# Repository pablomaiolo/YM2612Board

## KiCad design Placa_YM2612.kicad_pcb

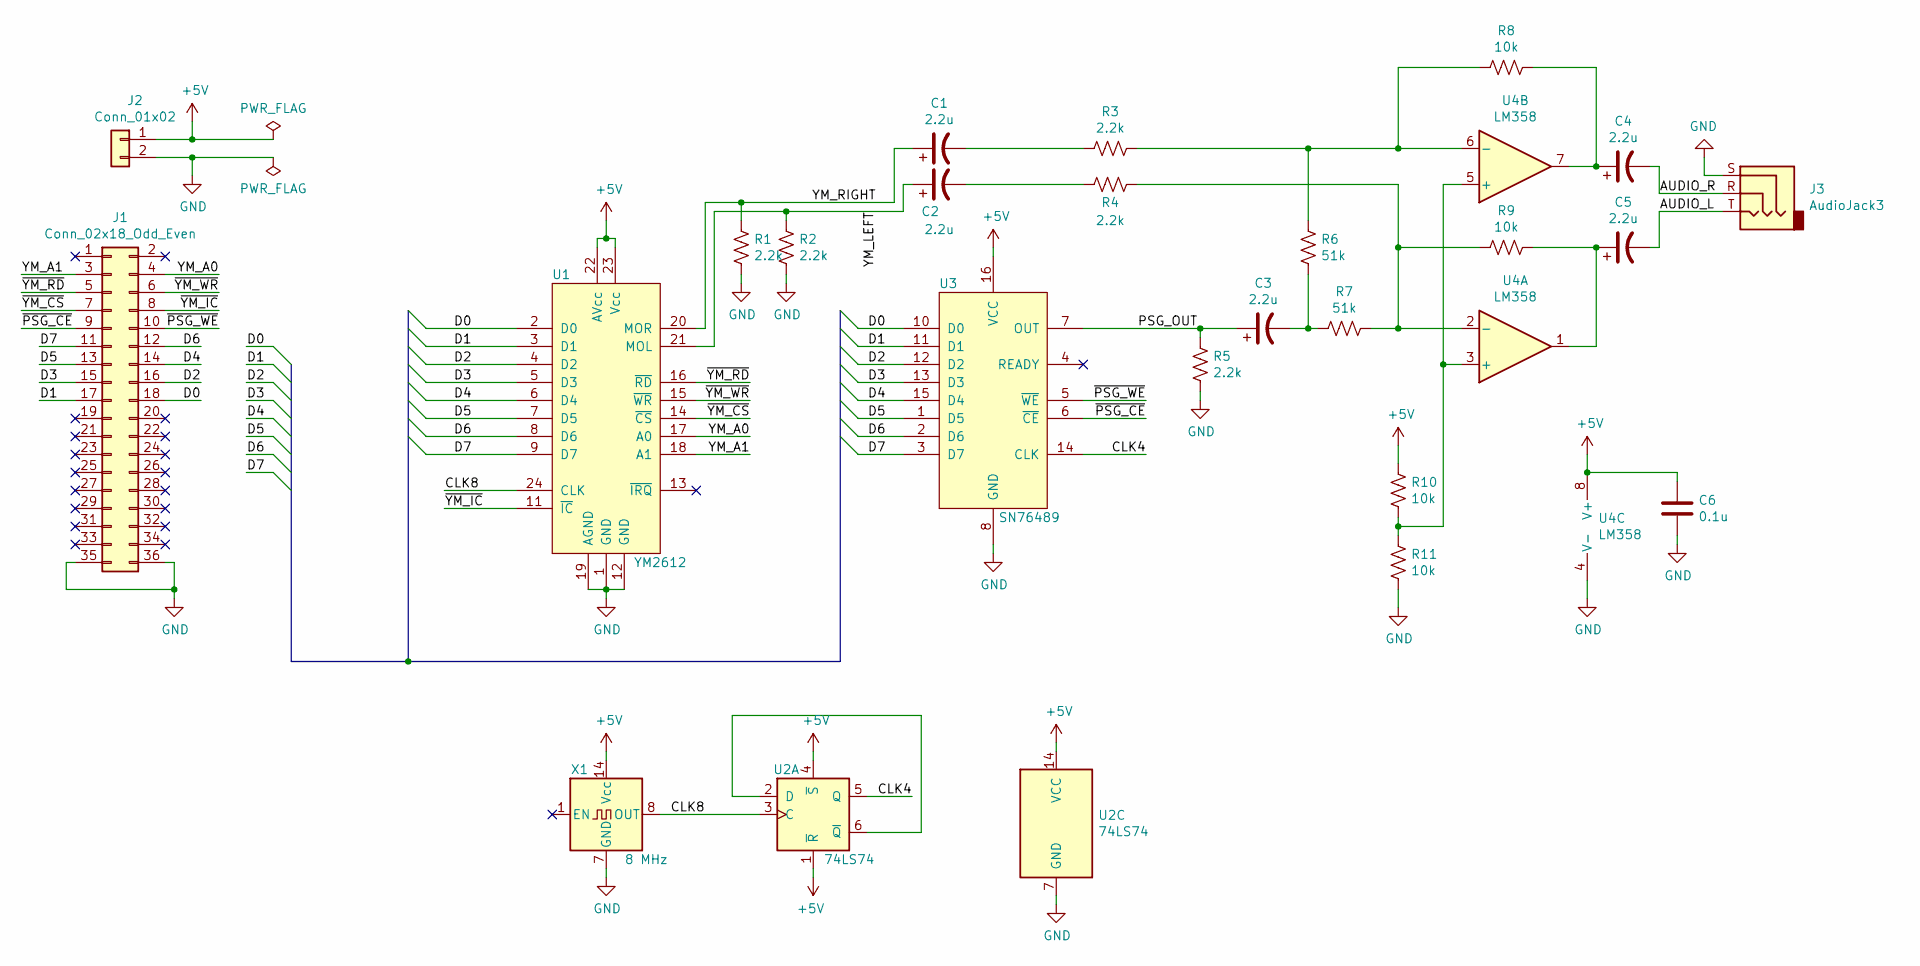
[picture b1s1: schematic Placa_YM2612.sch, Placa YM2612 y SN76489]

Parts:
C1, C2, C3, C4, C5: 2.2u; CP_Radial_D5.0mm_P2.50mm
C6: 0.1u; C_Disc_D5.0mm_W2.5mm_P2.50mm
J1: Conn_02x18_Odd_Even; PinHeader_2x18_P2.54mm_Vertical
J2: Conn_01x02; PinHeader_1x02_P2.54mm_Vertical
J3: AudioJack3; Placa_YM2612
R1, R2, R3, R4, R5: 2.2k; R_Axial_DIN0207_L6.3mm_D2.5mm_P10.16mm_Horizontal
R6, R7: 51k; R_Axial_DIN0207_L6.3mm_D2.5mm_P10.16mm_Horizontal
R8, R9, R10, R11: 10k; R_Axial_DIN0207_L6.3mm_D2.5mm_P10.16mm_Horizontal
U1: YM2612; DIP-24_W15.24mm_Socket_LongPads
U2: 74LS74; DIP-14_W7.62mm_LongPads
U3: SN76489; DIP-16_W7.62mm_Socket_LongPads
U4: LM358; DIP-8_W7.62mm_LongPads
X1: 8 MHz; Oscillator_DIP-14

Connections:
+5V: C6.1, J2.1, R10.1, U1.22 (AVcc), U1.23 (Vcc), U2.1 (~R), U2.4 (~S), U2.14 (VCC), U3.16 (VCC), U4.8 (V+), X1.14 (Vcc)
/AUDIO_L: C5.2, J3.T
/AUDIO_R: C4.2, J3.R
/CLK4: U2.5 (Q), U3.14 (CLK)
/CLK8: U1.24 (CLK), U2.3 (C), X1.8 (OUT)
/D0: J1.18, U1.2 (D0), U3.10 (D0)
/D1: J1.17, U1.3 (D1), U3.11 (D1)
/D2: J1.16, U1.4 (D2), U3.12 (D2)
/D3: J1.15, U1.5 (D3), U3.13 (D3)
/D4: J1.14, U1.6 (D4), U3.15 (D4)
/D5: J1.13, U1.7 (D5), U3.1 (D5)
/D6: J1.12, U1.8 (D6), U3.2 (D6)
/D7: J1.11, U1.9 (D7), U3.3 (D7)
/PSG_OUT: C3.1, R5.1, U3.7 (OUT)
/YM_A0: J1.4, U1.17 (A0)
/YM_A1: J1.3, U1.18 (A1)
/YM_LEFT: C2.1, R2.1, U1.21 (MOL)
/YM_RIGHT: C1.1, R1.1, U1.20 (MOR)
/~PSG_CE: J1.9, U3.6 (~CE)
/~PSG_WE: J1.10, U3.5 (~WE)
/~YM_CS: J1.7, U1.14 (~CS)
/~YM_IC: J1.8, U1.11 (~IC)
/~YM_RD: J1.5, U1.16 (~RD)
/~YM_WR: J1.6, U1.15 (~WR)
GND: C6.2, J1.35, J1.36, J2.2, J3.S, R1.2, R2.2, R5.2, R11.2, U1.1 (GND), U1.12 (GND), U1.19 (AGND), U2.7 (GND), U3.8 (GND), U4.4 (V-), X1.7 (GND)
unnamed: C1.2, R3.2
unnamed: C2.2, R4.2
unnamed: C3.2, R6.2, R7.2
unnamed: C4.1, R8.1, U4.7
unnamed: C5.1, R9.1, U4.1
unnamed: R3.1, R6.1, R8.2, U4.6 (-)
unnamed: R4.1, R7.1, R9.2, U4.2 (-)
unnamed: R10.2, R11.1, U4.3 (+), U4.5 (+)
unnamed: U2.2 (D), U2.6 (~Q)

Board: 2 copper layers, 25 parts (0 on the bottom side), 34 nets, no tracks yet.

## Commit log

2019-07-17 Commit inicial
2019-08-04 Placa a fabricar
2019-08-04 Corregidos nombres de los canales
2019-08-26 Cambiado TL072 por LM358, entre otras cosas
2019-09-15 Inicio de modificaciones para enviar a PCBWay
2022-06-06 Create LICENSE
